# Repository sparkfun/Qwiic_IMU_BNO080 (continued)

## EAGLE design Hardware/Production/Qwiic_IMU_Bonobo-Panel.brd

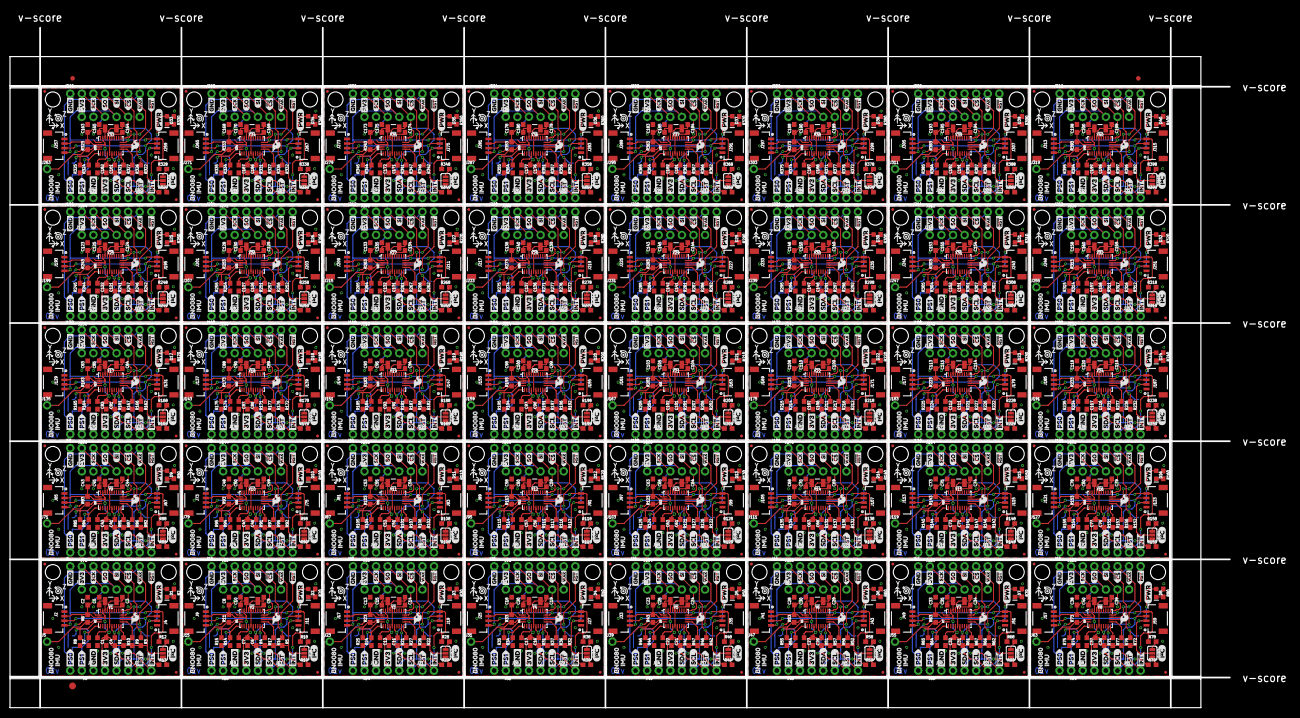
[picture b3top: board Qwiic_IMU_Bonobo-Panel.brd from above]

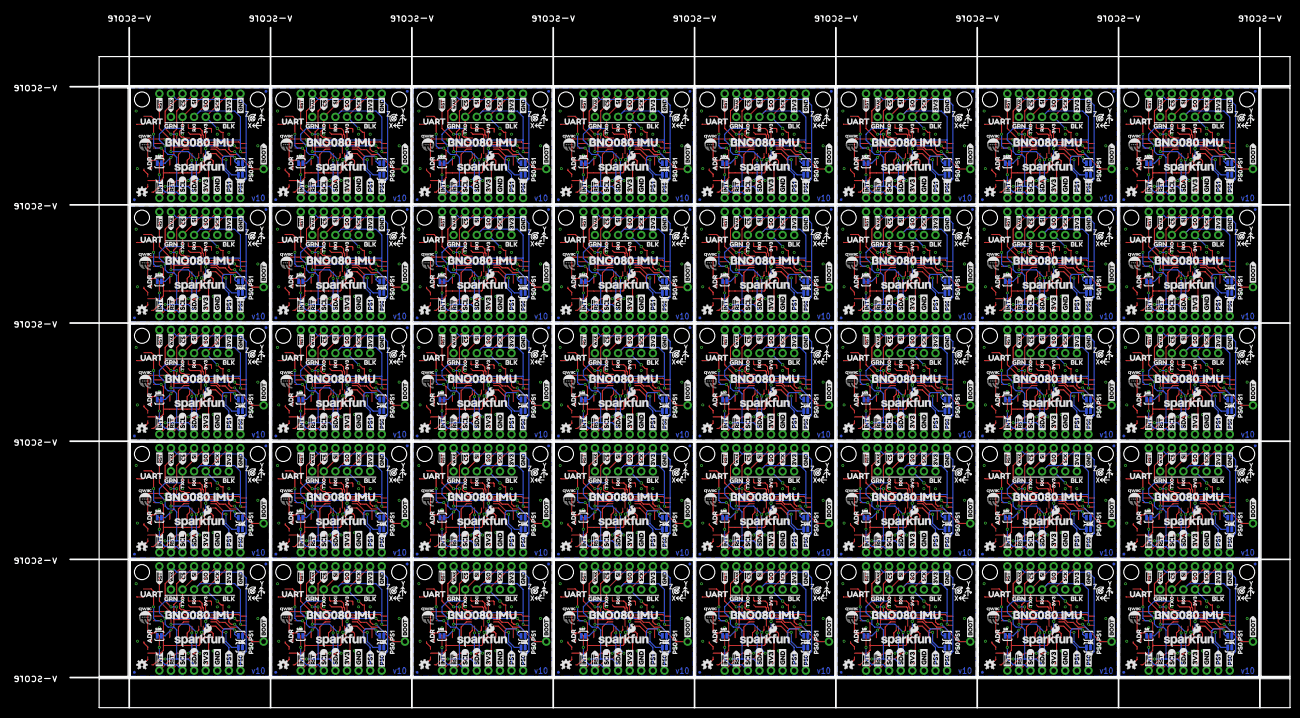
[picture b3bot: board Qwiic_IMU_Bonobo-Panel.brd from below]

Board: 2 copper layers, 267.5 x 149.1 mm, 3483 parts (1400 on the bottom side), 760 nets.

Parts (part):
C1, C2, C4, C6, C7, C8, C11, C12, C13, C16, C17, C18, C21, C22, C23, C26, C27, C28, C31, C32, C33, C36, C37, C38, C41, C42, C43, C46, C47, C48, C51, C52, C53, C56, C57, C58, C61, C62, C63, C66, C67, C68, C71, C72, C73, C76, C77, C78, C81, C82, C83, C86, C87, C88, C91, C92, C93, C96, C97, C98, C101, C102, C103, C106, C107, C108, C111, C112, C113, C116, C117, C118, C121, C122, C123, C126, C127, C128, C131, C132, C133, C136, C137, C138, C141, C142, C143, C146, C147, C148, C151, C152, C153, C156, C157, C158, C161, C162, C163, C166, C167, C168, C171, C172, C173, C176, C177, C178, C181, C182, C183, C186, C187, C188, C191, C192, C193, C196, C197, C198: 0.1uF; 0603
C3, C5, C9, C10, C14, C15, C19, C20, C24, C25, C29, C30, C34, C35, C39, C40, C44, C45, C49, C50, C54, C55, C59, C60, C64, C65, C69, C70, C74, C75, C79, C80, C84, C85, C89, C90, C94, C95, C99, C100, C104, C105, C109, C110, C114, C115, C119, C120, C124, C125, C129, C130, C134, C135, C139, C140, C144, C145, C149, C150, C154, C155, C159, C160, C164, C165, C169, C170, C174, C175, C179, C180, C184, C185, C189, C190, C194, C195, C199, C200: 22pF; 0603
D1, D2, D3, D4, D5, D6, D7, D8, D9, D10, D11, D12, D13, D14, D15, D16, D17, D18, D19, D20, D21, D22, D23, D24, D25, D26, D27, D28, D29, D30, D31, D32, D33, D34, D35, D36, D37, D38, D39, D40: RED; LED-0603
E$1, E$2: FIDUCIAL-1X2
E$3: FIDUCIAL-1.5X3
J1, J14, J22, J30, J38, J46, J54, J62, J70, J78, J86, J94, J102, J110, J118, J126, J134, J142, J150, J158, J166, J174, J182, J190, J198, J206, J214, J222, J230, J238, J246, J254, J262, J270, J278, J286, J294, J302, J310, J318: 1X06_NO_SILK
J2, J4, J9, J11, J17, J19, J25, J27, J33, J35, J41, J43, J49, J51, J57, J59, J65, J67, J73, J75, J81, J83, J89, J91, J97, J99, J105, J107, J113, J115, J121, J123, J129, J131, J137, J139, J145, J147, J153, J155, J161, J163, J169, J171, J177, J179, J185, J187, J193, J195, J201, J203, J209, J211, J217, J219, J225, J227, J233, J235, J241, J243, J249, J251, J257, J259, J265, J267, J273, J275, J281, J283, J289, J291, J297, J299, J305, J307, J313, J315: SMD; 1X04_1MM_RA
J3, J10, J18, J26, J34, J42, J50, J58, J66, J74, J82, J90, J98, J106, J114, J122, J130, J138, J146, J154, J162, J170, J178, J186, J194, J202, J210, J218, J226, J234, J242, J250, J258, J266, J274, J282, J290, J298, J306, J314: PTH; 1X04_NO_SILK
J5, J15, J23, J31, J39, J47, J55, J63, J71, J79, J87, J95, J103, J111, J119, J127, J135, J143, J151, J159, J167, J175, J183, J191, J199, J207, J215, J223, J231, J239, J247, J255, J263, J271, J279, J287, J295, J303, J311, J319: 1X01_NO_SILK
J6, J12, J20, J28, J36, J44, J52, J60, J68, J76, J84, J92, J100, J108, J116, J124, J132, J140, J148, J156, J164, J172, J180, J188, J196, J204, J212, J220, J228, J236, J244, J252, J260, J268, J276, J284, J292, J300, J308, J316: SPI; 1X08_NO_SILK
J7, J8, J13, J16, J21, J24, J29, J32, J37, J40, J45, J48, J53, J56, J61, J64, J69, J72, J77, J80, J85, J88, J93, J96, J101, J104, J109, J112, J117, J120, J125, J128, J133, J136, J141, J144, J149, J152, J157, J160, J165, J168, J173, J176, J181, J184, J189, J192, J197, J200, J205, J208, J213, J216, J221, J224, J229, J232, J237, J240, J245, J248, J253, J256, J261, J264, J269, J272, J277, J280, J285, J288, J293, J296, J301, J304, J309, J312, J317, J320: 1X02_NO_SILK
JP1, JP2, JP5, JP6, JP9, JP10, JP11, JP12, JP15, JP16, JP17, JP18, JP21, JP22, JP23, JP24, JP27, JP28, JP29, JP30, JP33, JP34, JP35, JP36, JP39, JP40, JP41, JP42, JP45, JP46, JP47, JP48, JP51, JP52, JP53, JP54, JP57, JP58, JP59, JP60, JP63, JP64, JP65, JP66, JP69, JP70, JP71, JP72, JP75, JP76, JP77, JP78, JP81, JP82, JP83, JP84, JP87, JP88, JP89, JP90, JP93, JP94, JP95, JP96, JP99, JP100, JP101, JP102, JP105, JP106, JP107, JP108, JP111, JP112, JP113, JP114, JP117, JP118, JP119, JP120, JP123, JP124, JP125, JP126, JP129, JP130, JP131, JP132, JP135, JP136, JP137, JP138, JP141, JP142, JP143, JP144, JP147, JP148, JP149, JP150, JP153, JP154, JP155, JP156, JP159, JP160, JP161, JP162, JP165, JP166, JP167, JP168, JP171, JP172, JP173, JP174, JP177, JP178, JP179, JP180, JP183, JP184, JP185, JP186, JP189, JP190, JP191, JP192, JP195, JP196, JP197, JP198, JP201, JP202, JP203, JP204, JP207, JP208, JP209, JP210, JP213, JP214, JP215, JP216, JP219, JP220, JP221, JP222, JP225, JP226, JP227, JP228, JP231, JP232, JP233, JP234, JP237, JP238, JP239, JP240: FIDUCIALUFIDUCIAL; MICRO-FIDUCIAL
JP3, JP4, JP7, JP8, JP13, JP14, JP19, JP20, JP25, JP26, JP31, JP32, JP37, JP38, JP43, JP44, JP49, JP50, JP55, JP56, JP61, JP62, JP67, JP68, JP73, JP74, JP79, JP80, JP85, JP86, JP91, JP92, JP97, JP98, JP103, JP104, JP109, JP110, JP115, JP116, JP121, JP122, JP127, JP128, JP133, JP134, JP139, JP140, JP145, JP146, JP151, JP152, JP157, JP158, JP163, JP164, JP169, JP170, JP175, JP176, JP181, JP182, JP187, JP188, JP193, JP194, JP199, JP200, JP205, JP206, JP211, JP212, JP217, JP218, JP223, JP224, JP229, JP230, JP235, JP236: STAND-OFF
LOGO1, LOGO2, LOGO7, LOGO10, LOGO13, LOGO16, LOGO19, LOGO22, LOGO25, LOGO28, LOGO31, LOGO34, LOGO37, LOGO40, LOGO43, LOGO46, LOGO49, LOGO52, LOGO55, LOGO58, LOGO61, LOGO64, LOGO67, LOGO70, LOGO73, LOGO76, LOGO79, LOGO82, LOGO85, LOGO88, LOGO91, LOGO94, LOGO97, LOGO100, LOGO103, LOGO106, LOGO109, LOGO112, LOGO115, LOGO118: OSHW-LOGOMINI; OSHW-LOGO-MINI
LOGO3, LOGO4, LOGO8, LOGO11, LOGO14, LOGO17, LOGO20, LOGO23, LOGO26, LOGO29, LOGO32, LOGO35, LOGO38, LOGO41, LOGO44, LOGO47, LOGO50, LOGO53, LOGO56, LOGO59, LOGO62, LOGO65, LOGO68, LOGO71, LOGO74, LOGO77, LOGO80, LOGO83, LOGO86, LOGO89, LOGO92, LOGO95, LOGO98, LOGO101, LOGO104, LOGO107, LOGO110, LOGO113, LOGO116, LOGO119: SFE_LOGO_FLAME.1_INCH; SFE_LOGO_FLAME_.1
LOGO5, LOGO6, LOGO9, LOGO12, LOGO15, LOGO18, LOGO21, LOGO24, LOGO27, LOGO30, LOGO33, LOGO36, LOGO39, LOGO42, LOGO45, LOGO48, LOGO51, LOGO54, LOGO57, LOGO60, LOGO63, LOGO66, LOGO69, LOGO72, LOGO75, LOGO78, LOGO81, LOGO84, LOGO87, LOGO90, LOGO93, LOGO96, LOGO99, LOGO102, LOGO105, LOGO108, LOGO111, LOGO114, LOGO117, LOGO120: SFE_LOGO_NAME_FLAME.1_INCH; SFE_LOGO_NAME_FLAME_.1
R1, R3, R4, R5, R6, R7, R8, R11, R14, R15, R21, R22, R23, R24, R25, R31, R32, R33, R34, R35, R41, R42, R43, R44, R45, R51, R52, R53, R54, R55, R61, R62, R63, R64, R65, R71, R72, R73, R74, R75, R81, R82, R83, R84, R85, R91, R92, R93, R94, R95, R101, R102, R103, R104, R105, R111, R112, R113, R114, R115, R121, R122, R123, R124, R125, R131, R132, R133, R134, R135, R141, R142, R143, R144, R145, R151, R152, R153, R154, R155, R161, R162, R163, R164, R165, R171, R172, R173, R174, R175, R181, R182, R183, R184, R185, R191, R192, R193, R194, R195, R201, R202, R203, R204, R205, R211, R212, R213, R214, R215, R221, R222, R223, R224, R225, R231, R232, R233, R234, R235, R241, R242, R243, R244, R245, R251, R252, R253, R254, R255, R261, R262, R263, R264, R265, R271, R272, R273, R274, R275, R281, R282, R283, R284, R285, R291, R292, R293, R294, R295, R301, R302, R303, R304, R305, R311, R312, R313, R314, R315, R321, R322, R323, R324, R325, R331, R332, R333, R334, R335, R341, R342, R343, R344, R345, R351, R352, R353, R354, R355, R361, R362, R363, R364, R365, R371, R372, R373, R374, R375, R381, R382, R383, R384, R385, R391, R392, R393, R394, R395: 10k; 0603
R2, R20, R30, R40, R50, R60, R70, R80, R90, R100, R110, R120, R130, R140, R150, R160, R170, R180, R190, R200, R210, R220, R230, R240, R250, R260, R270, R280, R290, R300, R310, R320, R330, R340, R350, R360, R370, R380, R390, R400: 1k; 0603
R9, R10, R16, R17, R26, R27, R36, R37, R46, R47, R56, R57, R66, R67, R76, R77, R86, R87, R96, R97, R106, R107, R116, R117, R126, R127, R136, R137, R146, R147, R156, R157, R166, R167, R176, R177, R186, R187, R196, R197, R206, R207, R216, R217, R226, R227, R236, R237, R246, R247, R256, R257, R266, R267, R276, R277, R286, R287, R296, R297, R306, R307, R316, R317, R326, R327, R336, R337, R346, R347, R356, R357, R366, R367, R376, R377, R386, R387, R396, R397: 4.7k; 0603
R12, R13, R18, R19, R28, R29, R38, R39, R48, R49, R58, R59, R68, R69, R78, R79, R88, R89, R98, R99, R108, R109, R118, R119, R128, R129, R138, R139, R148, R149, R158, R159, R168, R169, R178, R179, R188, R189, R198, R199, R208, R209, R218, R219, R228, R229, R238, R239, R248, R249, R258, R259, R268, R269, R278, R279, R288, R289, R298, R299, R308, R309, R318, R319, R328, R329, R338, R339, R348, R349, R358, R359, R368, R369, R378, R379, R388, R389, R398, R399: 2.2k; 0603
SJ1, SJ8, SJ12, SJ16, SJ20, SJ24, SJ28, SJ32, SJ36, SJ40, SJ44, SJ48, SJ52, SJ56, SJ60, SJ64, SJ68, SJ72, SJ76, SJ80, SJ84, SJ88, SJ92, SJ96, SJ100, SJ104, SJ108, SJ112, SJ116, SJ120, SJ124, SJ128, SJ132, SJ136, SJ140, SJ144, SJ148, SJ152, SJ156, SJ160: SMT-JUMPER_3_2-NC_PASTE_SILK
SJ2, SJ3, SJ4, SJ5, SJ6, SJ7, SJ9, SJ10, SJ11, SJ13, SJ14, SJ15, SJ17, SJ18, SJ19, SJ21, SJ22, SJ23, SJ25, SJ26, SJ27, SJ29, SJ30, SJ31, SJ33, SJ34, SJ35, SJ37, SJ38, SJ39, SJ41, SJ42, SJ43, SJ45, SJ46, SJ47, SJ49, SJ50, SJ51, SJ53, SJ54, SJ55, SJ57, SJ58, SJ59, SJ61, SJ62, SJ63, SJ65, SJ66, SJ67, SJ69, SJ70, SJ71, SJ73, SJ74, SJ75, SJ77, SJ78, SJ79, SJ81, SJ82, SJ83, SJ85, SJ86, SJ87, SJ89, SJ90, SJ91, SJ93, SJ94, SJ95, SJ97, SJ98, SJ99, SJ101, SJ102, SJ103, SJ105, SJ106, SJ107, SJ109, SJ110, SJ111, SJ113, SJ114, SJ115, SJ117, SJ118, SJ119, SJ121, SJ122, SJ123, SJ125, SJ126, SJ127, SJ129, SJ130, SJ131, SJ133, SJ134, SJ135, SJ137, SJ138, SJ139, SJ141, SJ142, SJ143, SJ145, SJ146, SJ147, SJ149, SJ150, SJ151, SJ153, SJ154, SJ155, SJ157, SJ158, SJ159: SJ_2S-NO
U1, U2, U3, U4, U5, U6, U7, U8, U9, U10, U11, U12, U13, U14, U15, U16, U17, U18, U19, U20, U21, U22, U23, U24, U25, U26, U27, U28, U29, U30, U31, U32, U33, U34, U35, U36, U37, U38, U39, U40: BNO080; LGA-28
U$1, U$95, U$143, U$191, U$239, U$287, U$335, U$383, U$431, U$479, U$527, U$575, U$623, U$671, U$719, U$767, U$815, U$863, U$911, U$959, U$1007, U$1055, U$1103, U$1151, U$1199, U$1247, U$1295, U$1343, U$1391, U$1439, U$1487, U$1535, U$1583, U$1631, U$1679, U$1727, U$1775, U$1823, U$1871, U$1919: (PWR)
U$2, U$94, U$142, U$190, U$238, U$286, U$334, U$382, U$430, U$478, U$526, U$574, U$622, U$670, U$718, U$766, U$814, U$862, U$910, U$958, U$1006, U$1054, U$1102, U$1150, U$1198, U$1246, U$1294, U$1342, U$1390, U$1438, U$1486, U$1534, U$1582, U$1630, U$1678, U$1726, U$1774, U$1822, U$1870, U$1918: BOOT2
U$3, U$4, U$24, U$31, U$97, U$98, U$145, U$146, U$193, U$194, U$241, U$242, U$289, U$290, U$337, U$338, U$385, U$386, U$433, U$434, U$481, U$482, U$529, U$530, U$577, U$578, U$625, U$626, U$673, U$674, U$721, U$722, U$769, U$770, U$817, U$818, U$865, U$866, U$913, U$914, U$961, U$962, U$1009, U$1010, U$1057, U$1058, U$1105, U$1106, U$1153, U$1154, U$1201, U$1202, U$1249, U$1250, U$1297, U$1298, U$1345, U$1346, U$1393, U$1394, U$1441, U$1442, U$1489, U$1490, U$1537, U$1538, U$1585, U$1586, U$1633, U$1634, U$1681, U$1682, U$1729, U$1730, U$1777, U$1778, U$1825, U$1826, U$1873, U$1874: #RST>
U$5, U$6, U$32, U$36, U$99, U$100, U$147, U$148, U$195, U$196, U$243, U$244, U$291, U$292, U$339, U$340, U$387, U$388, U$435, U$436, U$483, U$484, U$531, U$532, U$579, U$580, U$627, U$628, U$675, U$676, U$723, U$724, U$771, U$772, U$819, U$820, U$867, U$868, U$915, U$916, U$963, U$964, U$1011, U$1012, U$1059, U$1060, U$1107, U$1108, U$1155, U$1156, U$1203, U$1204, U$1251, U$1252, U$1299, U$1300, U$1347, U$1348, U$1395, U$1396, U$1443, U$1444, U$1491, U$1492, U$1539, U$1540, U$1587, U$1588, U$1635, U$1636, U$1683, U$1684, U$1731, U$1732, U$1779, U$1780, U$1827, U$1828, U$1875, U$1876: SCL
U$7, U$8, U$37, U$38, U$101, U$102, U$149, U$150, U$197, U$198, U$245, U$246, U$293, U$294, U$341, U$342, U$389, U$390, U$437, U$438, U$485, U$486, U$533, U$534, U$581, U$582, U$629, U$630, U$677, U$678, U$725, U$726, U$773, U$774, U$821, U$822, U$869, U$870, U$917, U$918, U$965, U$966, U$1013, U$1014, U$1061, U$1062, U$1109, U$1110, U$1157, U$1158, U$1205, U$1206, U$1253, U$1254, U$1301, U$1302, U$1349, U$1350, U$1397, U$1398, U$1445, U$1446, U$1493, U$1494, U$1541, U$1542, U$1589, U$1590, U$1637, U$1638, U$1685, U$1686, U$1733, U$1734, U$1781, U$1782, U$1829, U$1830, U$1877, U$1878: SDA
U$9, U$10, U$45, U$48, U$103, U$104, U$151, U$152, U$199, U$200, U$247, U$248, U$295, U$296, U$343, U$344, U$391, U$392, U$439, U$440, U$487, U$488, U$535, U$536, U$583, U$584, U$631, U$632, U$679, U$680, U$727, U$728, U$775, U$776, U$823, U$824, U$871, U$872, U$919, U$920, U$967, U$968, U$1015, U$1016, U$1063, U$1064, U$1111, U$1112, U$1159, U$1160, U$1207, U$1208, U$1255, U$1256, U$1303, U$1304, U$1351, U$1352, U$1399, U$1400, U$1447, U$1448, U$1495, U$1496, U$1543, U$1544, U$1591, U$1592, U$1639, U$1640, U$1687, U$1688, U$1735, U$1736, U$1783, U$1784, U$1831, U$1832, U$1879, U$1880: 3V3
U$11, U$50, U$73, U$74, U$121, U$122, U$169, U$170, U$217, U$218, U$265, U$266, U$313, U$314, U$361, U$362, U$409, U$410, U$457, U$458, U$505, U$506, U$553, U$554, U$601, U$602, U$649, U$650, U$697, U$698, U$745, U$746, U$793, U$794, U$841, U$842, U$889, U$890, U$937, U$938, U$985, U$986, U$1033, U$1034, U$1081, U$1082, U$1129, U$1130, U$1177, U$1178, U$1225, U$1226, U$1273, U$1274, U$1321, U$1322, U$1369, U$1370, U$1417, U$1418, U$1465, U$1466, U$1513, U$1514, U$1561, U$1562, U$1609, U$1610, U$1657, U$1658, U$1705, U$1706, U$1753, U$1754, U$1801, U$1802, U$1849, U$1850, U$1897, U$1898: 3V30
U$12, U$13, U$83, U$84, U$131, U$132, U$179, U$180, U$227, U$228, U$275, U$276, U$323, U$324, U$371, U$372, U$419, U$420, U$467, U$468, U$515, U$516, U$563, U$564, U$611, U$612, U$659, U$660, U$707, U$708, U$755, U$756, U$803, U$804, U$851, U$852, U$899, U$900, U$947, U$948, U$995, U$996, U$1043, U$1044, U$1091, U$1092, U$1139, U$1140, U$1187, U$1188, U$1235, U$1236, U$1283, U$1284, U$1331, U$1332, U$1379, U$1380, U$1427, U$1428, U$1475, U$1476, U$1523, U$1524, U$1571, U$1572, U$1619, U$1620, U$1667, U$1668, U$1715, U$1716, U$1763, U$1764, U$1811, U$1812, U$1859, U$1860, U$1907, U$1908: SCK0
U$14, U$89, U$137, U$185, U$233, U$281, U$329, U$377, U$425, U$473, U$521, U$569, U$617, U$665, U$713, U$761, U$809, U$857, U$905, U$953, U$1001, U$1049, U$1097, U$1145, U$1193, U$1241, U$1289, U$1337, U$1385, U$1433, U$1481, U$1529, U$1577, U$1625, U$1673, U$1721, U$1769, U$1817, U$1865, U$1913: PS03
U$15, U$16, U$56, U$57, U$105, U$106, U$153, U$154, U$201, U$202, U$249, U$250, U$297, U$298, U$345, U$346, U$393, U$394, U$441, U$442, U$489, U$490, U$537, U$538, U$585, U$586, U$633, U$634, U$681, U$682, U$729, U$730, U$777, U$778, U$825, U$826, U$873, U$874, U$921, U$922, U$969, U$970, U$1017, U$1018, U$1065, U$1066, U$1113, U$1114, U$1161, U$1162, U$1209, U$1210, U$1257, U$1258, U$1305, U$1306, U$1353, U$1354, U$1401, U$1402, U$1449, U$1450, U$1497, U$1498, U$1545, U$1546, U$1593, U$1594, U$1641, U$1642, U$1689, U$1690, U$1737, U$1738, U$1785, U$1786, U$1833, U$1834, U$1881, U$1882: GND
U$17, U$18, U$85, U$86, U$133, U$134, U$181, U$182, U$229, U$230, U$277, U$278, U$325, U$326, U$373, U$374, U$421, U$422, U$469, U$470, U$517, U$518, U$565, U$566, U$613, U$614, U$661, U$662, U$709, U$710, U$757, U$758, U$805, U$806, U$853, U$854, U$901, U$902, U$949, U$950, U$997, U$998, U$1045, U$1046, U$1093, U$1094, U$1141, U$1142, U$1189, U$1190, U$1237, U$1238, U$1285, U$1286, U$1333, U$1334, U$1381, U$1382, U$1429, U$1430, U$1477, U$1478, U$1525, U$1526, U$1573, U$1574, U$1621, U$1622, U$1669, U$1670, U$1717, U$1718, U$1765, U$1766, U$1813, U$1814, U$1861, U$1862, U$1909, U$1910: SI1
U$19, U$20, U$77, U$78, U$125, U$126, U$173, U$174, U$221, U$222, U$269, U$270, U$317, U$318, U$365, U$366, U$413, U$414, U$461, U$462, U$509, U$510, U$557, U$558, U$605, U$606, U$653, U$654, U$701, U$702, U$749, U$750, U$797, U$798, U$845, U$846, U$893, U$894, U$941, U$942, U$989, U$990, U$1037, U$1038, U$1085, U$1086, U$1133, U$1134, U$1181, U$1182, U$1229, U$1230, U$1277, U$1278, U$1325, U$1326, U$1373, U$1374, U$1421, U$1422, U$1469, U$1470, U$1517, U$1518, U$1565, U$1566, U$1613, U$1614, U$1661, U$1662, U$1709, U$1710, U$1757, U$1758, U$1805, U$1806, U$1853, U$1854, U$1901, U$1902: #WAK6
U$21, U$90, U$138, U$186, U$234, U$282, U$330, U$378, U$426, U$474, U$522, U$570, U$618, U$666, U$714, U$762, U$810, U$858, U$906, U$954, U$1002, U$1050, U$1098, U$1146, U$1194, U$1242, U$1290, U$1338, U$1386, U$1434, U$1482, U$1530, U$1578, U$1626, U$1674, U$1722, U$1770, U$1818, U$1866, U$1914: 3V32
U$22, U$91, U$139, U$187, U$235, U$283, U$331, U$379, U$427, U$475, U$523, U$571, U$619, U$667, U$715, U$763, U$811, U$859, U$907, U$955, U$1003, U$1051, U$1099, U$1147, U$1195, U$1243, U$1291, U$1339, U$1387, U$1435, U$1483, U$1531, U$1579, U$1627, U$1675, U$1723, U$1771, U$1819, U$1867, U$1915: RXI1
U$23, U$58, U$107, U$155, U$203, U$251, U$299, U$347, U$395, U$443, U$491, U$539, U$587, U$635, U$683, U$731, U$779, U$827, U$875, U$923, U$971, U$1019, U$1067, U$1115, U$1163, U$1211, U$1259, U$1307, U$1355, U$1403, U$1451, U$1499, U$1547, U$1595, U$1643, U$1691, U$1739, U$1787, U$1835, U$1883: (I_SUPER2_C)
U$25, U$26, U$60, U$61, U$108, U$109, U$156, U$157, U$204, U$205, U$252, U$253, U$300, U$301, U$348, U$349, U$396, U$397, U$444, U$445, U$492, U$493, U$540, U$541, U$588, U$589, U$636, U$637, U$684, U$685, U$732, U$733, U$780, U$781, U$828, U$829, U$876, U$877, U$924, U$925, U$972, U$973, U$1020, U$1021, U$1068, U$1069, U$1116, U$1117, U$1164, U$1165, U$1212, U$1213, U$1260, U$1261, U$1308, U$1309, U$1356, U$1357, U$1404, U$1405, U$1452, U$1453, U$1500, U$1501, U$1548, U$1549, U$1596, U$1597, U$1644, U$1645, U$1692, U$1693, U$1740, U$1741, U$1788, U$1789, U$1836, U$1837, U$1884, U$1885: #INT0
U$27, U$28, U$62, U$63, U$110, U$111, U$158, U$159, U$206, U$207, U$254, U$255, U$302, U$303, U$350, U$351, U$398, U$399, U$446, U$447, U$494, U$495, U$542, U$543, U$590, U$591, U$638, U$639, U$686, U$687, U$734, U$735, U$782, U$783, U$830, U$831, U$878, U$879, U$926, U$927, U$974, U$975, U$1022, U$1023, U$1070, U$1071, U$1118, U$1119, U$1166, U$1167, U$1214, U$1215, U$1262, U$1263, U$1310, U$1311, U$1358, U$1359, U$1406, U$1407, U$1454, U$1455, U$1502, U$1503, U$1550, U$1551, U$1598, U$1599, U$1646, U$1647, U$1694, U$1695, U$1742, U$1743, U$1790, U$1791, U$1838, U$1839, U$1886, U$1887: PS14
U$29, U$64, U$112, U$160, U$208, U$256, U$304, U$352, U$400, U$448, U$496, U$544, U$592, U$640, U$688, U$736, U$784, U$832, U$880, U$928, U$976, U$1024, U$1072, U$1120, U$1168, U$1216, U$1264, U$1312, U$1360, U$1408, U$1456, U$1504, U$1552, U$1600, U$1648, U$1696, U$1744, U$1792, U$1840, U$1888: PS05
U$30, U$93, U$141, U$189, U$237, U$285, U$333, U$381, U$429, U$477, U$525, U$573, U$621, U$669, U$717, U$765, U$813, U$861, U$909, U$957, U$1005, U$1053, U$1101, U$1149, U$1197, U$1245, U$1293, U$1341, U$1389, U$1437, U$1485, U$1533, U$1581, U$1629, U$1677, U$1725, U$1773, U$1821, U$1869, U$1917: ADR0
U$33, U$65, U$113, U$161, U$209, U$257, U$305, U$353, U$401, U$449, U$497, U$545, U$593, U$641, U$689, U$737, U$785, U$833, U$881, U$929, U$977, U$1025, U$1073, U$1121, U$1169, U$1217, U$1265, U$1313, U$1361, U$1409, U$1457, U$1505, U$1553, U$1601, U$1649, U$1697, U$1745, U$1793, U$1841, U$1889: PS114
U$34, U$66, U$114, U$162, U$210, U$258, U$306, U$354, U$402, U$450, U$498, U$546, U$594, U$642, U$690, U$738, U$786, U$834, U$882, U$930, U$978, U$1026, U$1074, U$1122, U$1170, U$1218, U$1266, U$1314, U$1362, U$1410, U$1458, U$1506, U$1554, U$1602, U$1650, U$1698, U$1746, U$1794, U$1842, U$1890: PS015
U$35, U$92, U$140, U$188, U$236, U$284, U$332, U$380, U$428, U$476, U$524, U$572, U$620, U$668, U$716, U$764, U$812, U$860, U$908, U$956, U$1004, U$1052, U$1100, U$1148, U$1196, U$1244, U$1292, U$1340, U$1388, U$1436, U$1484, U$1532, U$1580, U$1628, U$1676, U$1724, U$1772, U$1820, U$1868, U$1916: TXO0
U$39, U$67, U$115, U$163, U$211, U$259, U$307, U$355, U$403, U$451, U$499, U$547, U$595, U$643, U$691, U$739, U$787, U$835, U$883, U$931, U$979, U$1027, U$1075, U$1123, U$1171, U$1219, U$1267, U$1315, U$1363, U$1411, U$1459, U$1507, U$1555, U$1603, U$1651, U$1699, U$1747, U$1795, U$1843, U$1891: UART8
U$40, U$68, U$116, U$164, U$212, U$260, U$308, U$356, U$404, U$452, U$500, U$548, U$596, U$644, U$692, U$740, U$788, U$836, U$884, U$932, U$980, U$1028, U$1076, U$1124, U$1172, U$1220, U$1268, U$1316, U$1364, U$1412, U$1460, U$1508, U$1556, U$1604, U$1652, U$1700, U$1748, U$1796, U$1844, U$1892: GRN10
U$41, U$69, U$117, U$165, U$213, U$261, U$309, U$357, U$405, U$453, U$501, U$549, U$597, U$645, U$693, U$741, U$789, U$837, U$885, U$933, U$981, U$1029, U$1077, U$1125, U$1173, U$1221, U$1269, U$1317, U$1365, U$1413, U$1461, U$1509, U$1557, U$1605, U$1653, U$1701, U$1749, U$1797, U$1845, U$1893: BLK9
U$42, U$43, U$79, U$80, U$127, U$128, U$175, U$176, U$223, U$224, U$271, U$272, U$319, U$320, U$367, U$368, U$415, U$416, U$463, U$464, U$511, U$512, U$559, U$560, U$607, U$608, U$655, U$656, U$703, U$704, U$751, U$752, U$799, U$800, U$847, U$848, U$895, U$896, U$943, U$944, U$991, U$992, U$1039, U$1040, U$1087, U$1088, U$1135, U$1136, U$1183, U$1184, U$1231, U$1232, U$1279, U$1280, U$1327, U$1328, U$1375, U$1376, U$1423, U$1424, U$1471, U$1472, U$1519, U$1520, U$1567, U$1568, U$1615, U$1616, U$1663, U$1664, U$1711, U$1712, U$1759, U$1760, U$1807, U$1808, U$1855, U$1856, U$1903, U$1904: GND1
U$44, U$70, U$118, U$166, U$214, U$262, U$310, U$358, U$406, U$454, U$502, U$550, U$598, U$646, U$694, U$742, U$790, U$838, U$886, U$934, U$982, U$1030, U$1078, U$1126, U$1174, U$1222, U$1270, U$1318, U$1366, U$1414, U$1462, U$1510, U$1558, U$1606, U$1654, U$1702, U$1750, U$1798, U$1846, U$1894: BNO080_IMU11
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
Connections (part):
3.3V: C2.1, C4.1, D1.A, J1.3, J2.2, J3.2, J4.2, J6.2, R1.2, R3.2, R6.2, R9.2, R10.2, SJ1.2, SJ3.1, SJ4.1, U2.3, U2.28
3.3V1: C6.1, C8.1, D2.A, J9.2, J10.2, J11.2, J12.2, J14.3, R4.2, R5.2, R11.2, R16.2, R17.2, SJ6.1, SJ7.1, SJ8.2, U1.3, U1.28
3.3V2: C11.1, C13.1, D3.A, J17.2, J18.2, J19.2, J20.2, J22.3, R21.2, R22.2, R23.2, R26.2, R27.2, SJ10.1, SJ11.1, SJ12.2, U3.3, U3.28
3.3V3: C16.1, C18.1, D4.A, J25.2, J26.2, J27.2, J28.2, J30.3, R31.2, R32.2, R33.2, R36.2, R37.2, SJ14.1, SJ15.1, SJ16.2, U4.3, U4.28
3.3V4: C21.1, C23.1, D5.A, J33.2, J34.2, J35.2, J36.2, J38.3, R41.2, R42.2, R43.2, R46.2, R47.2, SJ18.1, SJ19.1, SJ20.2, U5.3, U5.28
3.3V5: C26.1, C28.1, D6.A, J41.2, J42.2, J43.2, J44.2, J46.3, R51.2, R52.2, R53.2, R56.2, R57.2, SJ22.1, SJ23.1, SJ24.2, U6.3, U6.28
3.3V6: C31.1, C33.1, D7.A, J49.2, J50.2, J51.2, J52.2, J54.3, R61.2, R62.2, R63.2, R66.2, R67.2, SJ26.1, SJ27.1, SJ28.2, U7.3, U7.28
3.3V7: C36.1, C38.1, D8.A, J57.2, J58.2, J59.2, J60.2, J62.3, R71.2, R72.2, R73.2, R76.2, R77.2, SJ30.1, SJ31.1, SJ32.2, U8.3, U8.28
3.3V8: C41.1, C43.1, D9.A, J65.2, J66.2, J67.2, J68.2, J70.3, R81.2, R82.2, R83.2, R86.2, R87.2, SJ34.1, SJ35.1, SJ36.2, U9.3, U9.28
3.3V9: C46.1, C48.1, D10.A, J73.2, J74.2, J75.2, J76.2, J78.3, R91.2, R92.2, R93.2, R96.2, R97.2, SJ38.1, SJ39.1, SJ40.2, U10.3, U10.28
3.3V10: C51.1, C53.1, D11.A, J81.2, J82.2, J83.2, J84.2, J86.3, R101.2, R102.2, R103.2, R106.2, R107.2, SJ42.1, SJ43.1, SJ44.2, U11.3, U11.28
3.3V11: C56.1, C58.1, D12.A, J89.2, J90.2, J91.2, J92.2, J94.3, R111.2, R112.2, R113.2, R116.2, R117.2, SJ46.1, SJ47.1, SJ48.2, U12.3, U12.28
3.3V12: C61.1, C63.1, D13.A, J97.2, J98.2, J99.2, J100.2, J102.3, R121.2, R122.2, R123.2, R126.2, R127.2, SJ50.1, SJ51.1, SJ52.2, U13.3, U13.28
3.3V13: C66.1, C68.1, D14.A, J105.2, J106.2, J107.2, J108.2, J110.3, R131.2, R132.2, R133.2, R136.2, R137.2, SJ54.1, SJ55.1, SJ56.2, U14.3, U14.28
3.3V14: C71.1, C73.1, D15.A, J113.2, J114.2, J115.2, J116.2, J118.3, R141.2, R142.2, R143.2, R146.2, R147.2, SJ58.1, SJ59.1, SJ60.2, U15.3, U15.28
3.3V15: C76.1, C78.1, D16.A, J121.2, J122.2, J123.2, J124.2, J126.3, R151.2, R152.2, R153.2, R156.2, R157.2, SJ62.1, SJ63.1, SJ64.2, U16.3, U16.28
3.3V16: C81.1, C83.1, D17.A, J129.2, J130.2, J131.2, J132.2, J134.3, R161.2, R162.2, R163.2, R166.2, R167.2, SJ66.1, SJ67.1, SJ68.2, U17.3, U17.28
3.3V17: C86.1, C88.1, D18.A, J137.2, J138.2, J139.2, J140.2, J142.3, R171.2, R172.2, R173.2, R176.2, R177.2, SJ70.1, SJ71.1, SJ72.2, U18.3, U18.28
3.3V18: C91.1, C93.1, D19.A, J145.2, J146.2, J147.2, J148.2, J150.3, R181.2, R182.2, R183.2, R186.2, R187.2, SJ74.1, SJ75.1, SJ76.2, U19.3, U19.28
3.3V19: C96.1, C98.1, D20.A, J153.2, J154.2, J155.2, J156.2, J158.3, R191.2, R192.2, R193.2, R196.2, R197.2, SJ78.1, SJ79.1, SJ80.2, U20.3, U20.28
3.3V20: C101.1, C103.1, D21.A, J161.2, J162.2, J163.2, J164.2, J166.3, R201.2, R202.2, R203.2, R206.2, R207.2, SJ82.1, SJ83.1, SJ84.2, U21.3, U21.28
3.3V21: C106.1, C108.1, D22.A, J169.2, J170.2, J171.2, J172.2, J174.3, R211.2, R212.2, R213.2, R216.2, R217.2, SJ86.1, SJ87.1, SJ88.2, U22.3, U22.28
3.3V22: C111.1, C113.1, D23.A, J177.2, J178.2, J179.2, J180.2, J182.3, R221.2, R222.2, R223.2, R226.2, R227.2, SJ90.1, SJ91.1, SJ92.2, U23.3, U23.28
3.3V23: C116.1, C118.1, D24.A, J185.2, J186.2, J187.2, J188.2, J190.3, R231.2, R232.2, R233.2, R236.2, R237.2, SJ94.1, SJ95.1, SJ96.2, U24.3, U24.28
3.3V24: C121.1, C123.1, D25.A, J193.2, J194.2, J195.2, J196.2, J198.3, R241.2, R242.2, R243.2, R246.2, R247.2, SJ98.1, SJ99.1, SJ100.2, U25.3, U25.28
3.3V25: C126.1, C128.1, D26.A, J201.2, J202.2, J203.2, J204.2, J206.3, R251.2, R252.2, R253.2, R256.2, R257.2, SJ102.1, SJ103.1, SJ104.2, U26.3, U26.28
3.3V26: C131.1, C133.1, D27.A, J209.2, J210.2, J211.2, J212.2, J214.3, R261.2, R262.2, R263.2, R266.2, R267.2, SJ106.1, SJ107.1, SJ108.2, U27.3, U27.28
3.3V27: C136.1, C138.1, D28.A, J217.2, J218.2, J219.2, J220.2, J222.3, R271.2, R272.2, R273.2, R276.2, R277.2, SJ110.1, SJ111.1, SJ112.2, U28.3, U28.28
3.3V28: C141.1, C143.1, D29.A, J225.2, J226.2, J227.2, J228.2, J230.3, R281.2, R282.2, R283.2, R286.2, R287.2, SJ114.1, SJ115.1, SJ116.2, U29.3, U29.28
3.3V29: C146.1, C148.1, D30.A, J233.2, J234.2, J235.2, J236.2, J238.3, R291.2, R292.2, R293.2, R296.2, R297.2, SJ118.1, SJ119.1, SJ120.2, U30.3, U30.28
3.3V30: C151.1, C153.1, D31.A, J241.2, J242.2, J243.2, J244.2, J246.3, R301.2, R302.2, R303.2, R306.2, R307.2, SJ122.1, SJ123.1, SJ124.2, U31.3, U31.28
3.3V31: C156.1, C158.1, D32.A, J249.2, J250.2, J251.2, J252.2, J254.3, R311.2, R312.2, R313.2, R316.2, R317.2, SJ126.1, SJ127.1, SJ128.2, U32.3, U32.28
3.3V32: C161.1, C163.1, D33.A, J257.2, J258.2, J259.2, J260.2, J262.3, R321.2, R322.2, R323.2, R326.2, R327.2, SJ130.1, SJ131.1, SJ132.2, U33.3, U33.28
3.3V33: C166.1, C168.1, D34.A, J265.2, J266.2, J267.2, J268.2, J270.3, R331.2, R332.2, R333.2, R336.2, R337.2, SJ134.1, SJ135.1, SJ136.2, U34.3, U34.28
3.3V34: C171.1, C173.1, D35.A, J273.2, J274.2, J275.2, J276.2, J278.3, R341.2, R342.2, R343.2, R346.2, R347.2, SJ138.1, SJ139.1, SJ140.2, U35.3, U35.28
3.3V35: C176.1, C178.1, D36.A, J281.2, J282.2, J283.2, J284.2, J286.3, R351.2, R352.2, R353.2, R356.2, R357.2, SJ142.1, SJ143.1, SJ144.2, U36.3, U36.28
3.3V36: C181.1, C183.1, D37.A, J289.2, J290.2, J291.2, J292.2, J294.3, R361.2, R362.2, R363.2, R366.2, R367.2, SJ146.1, SJ147.1, SJ148.2, U37.3, U37.28
3.3V37: C186.1, C188.1, D38.A, J297.2, J298.2, J299.2, J300.2, J302.3, R371.2, R372.2, R373.2, R376.2, R377.2, SJ150.1, SJ151.1, SJ152.2, U38.3, U38.28
3.3V38: C191.1, C193.1, D39.A, J305.2, J306.2, J307.2, J308.2, J310.3, R381.2, R382.2, R383.2, R386.2, R387.2, SJ154.1, SJ155.1, SJ156.2, U39.3, U39.28
3.3V39: C196.1, C198.1, D40.A, J313.2, J314.2, J315.2, J316.2, J318.3, R391.2, R392.2, R393.2, R396.2, R397.2, SJ158.1, SJ159.1, SJ160.2, U40.3, U40.28
!BOOT: J5.1, R6.1, U2.4
!BOOT1: J15.1, R11.1, U1.4
!BOOT2: J23.1, R23.1, U3.4
!BOOT3: J31.1, R33.1, U4.4
!BOOT4: J39.1, R43.1, U5.4
!BOOT5: J47.1, R53.1, U6.4
!BOOT6: J55.1, R63.1, U7.4
!BOOT7: J63.1, R73.1, U8.4
!BOOT8: J71.1, R83.1, U9.4
!BOOT9: J79.1, R93.1, U10.4
!BOOT10: J87.1, R103.1, U11.4
!BOOT11: J95.1, R113.1, U12.4
!BOOT12: J103.1, R123.1, U13.4
!BOOT13: J111.1, R133.1, U14.4
!BOOT14: J119.1, R143.1, U15.4
!BOOT15: J127.1, R153.1, U16.4
!BOOT16: J135.1, R163.1, U17.4
!BOOT17: J143.1, R173.1, U18.4
!BOOT18: J151.1, R183.1, U19.4
!BOOT19: J159.1, R193.1, U20.4
!BOOT20: J167.1, R203.1, U21.4
!BOOT21: J175.1, R213.1, U22.4
!BOOT22: J183.1, R223.1, U23.4
!BOOT23: J191.1, R233.1, U24.4
!BOOT24: J199.1, R243.1, U25.4
!BOOT25: J207.1, R253.1, U26.4
!BOOT26: J215.1, R263.1, U27.4
!BOOT27: J223.1, R273.1, U28.4
!BOOT28: J231.1, R283.1, U29.4
!BOOT29: J239.1, R293.1, U30.4
!BOOT30: J247.1, R303.1, U31.4
!BOOT31: J255.1, R313.1, U32.4
!BOOT32: J263.1, R323.1, U33.4
!BOOT33: J271.1, R333.1, U34.4
!BOOT34: J279.1, R343.1, U35.4
!BOOT35: J287.1, R353.1, U36.4
!BOOT36: J295.1, R363.1, U37.4
!BOOT37: J303.1, R373.1, U38.4
!BOOT38: J311.1, R383.1, U39.4
!BOOT39: J319.1, R393.1, U40.4
!CS: J6.6, U2.18
!CS1: J12.6, U1.18
!CS2: J20.6, U3.18
!CS3: J28.6, U4.18
!CS4: J36.6, U5.18
!CS5: J44.6, U6.18
!CS6: J52.6, U7.18
!CS7: J60.6, U8.18
!CS8: J68.6, U9.18
!CS9: J76.6, U10.18
!CS10: J84.6, U11.18
!CS11: J92.6, U12.18
!CS12: J100.6, U13.18
!CS13: J108.6, U14.18
!CS14: J116.6, U15.18
!CS15: J124.6, U16.18
!CS16: J132.6, U17.18
!CS17: J140.6, U18.18
!CS18: J148.6, U19.18
!CS19: J156.6, U20.18
!CS20: J164.6, U21.18
!CS21: J172.6, U22.18
!CS22: J180.6, U23.18
!CS23: J188.6, U24.18
!CS24: J196.6, U25.18
!CS25: J204.6, U26.18
!CS26: J212.6, U27.18
!CS27: J220.6, U28.18
!CS28: J228.6, U29.18
!CS29: J236.6, U30.18
!CS30: J244.6, U31.18
!CS31: J252.6, U32.18
!CS32: J260.6, U33.18
!CS33: J268.6, U34.18
!CS34: J276.6, U35.18
!CS35: J284.6, U36.18
!CS36: J292.6, U37.18
!CS37: J300.6, U38.18
!CS38: J308.6, U39.18
!CS39: J316.6, U40.18
!INT: J7.2, U2.14
!INT1: J13.2, U1.14
!INT2: J21.2, U3.14
!INT3: J29.2, U4.14
!INT4: J37.2, U5.14
!INT5: J45.2, U6.14
!INT6: J53.2, U7.14
!INT7: J61.2, U8.14
!INT8: J69.2, U9.14
!INT9: J77.2, U10.14
!INT10: J85.2, U11.14
!INT11: J93.2, U12.14
!INT12: J101.2, U13.14
!INT13: J109.2, U14.14
!INT14: J117.2, U15.14
!INT15: J125.2, U16.14
!INT16: J133.2, U17.14
!INT17: J141.2, U18.14
!INT18: J149.2, U19.14
!INT19: J157.2, U20.14
!INT20: J165.2, U21.14
!INT21: J173.2, U22.14
!INT22: J181.2, U23.14
!INT23: J189.2, U24.14
!INT24: J197.2, U25.14
!INT25: J205.2, U26.14
!INT26: J213.2, U27.14
!INT27: J221.2, U28.14
!INT28: J229.2, U29.14
!INT29: J237.2, U30.14
!INT30: J245.2, U31.14
!INT31: J253.2, U32.14
!INT32: J261.2, U33.14
!INT33: J269.2, U34.14
!INT34: J277.2, U35.14
!INT35: J285.2, U36.14
!INT36: J293.2, U37.14
!INT37: J301.2, U38.14
!INT38: J309.2, U39.14
!INT39: J317.2, U40.14
!RST: J6.8, J7.1, R1.1, U2.11
!RST1: J12.8, J13.1, R4.1, U1.11
!RST2: J20.8, J21.1, R21.1, U3.11
!RST3: J28.8, J29.1, R31.1, U4.11
!RST4: J36.8, J37.1, R41.1, U5.11
!RST5: J44.8, J45.1, R51.1, U6.11
!RST6: J52.8, J53.1, R61.1, U7.11
!RST7: J60.8, J61.1, R71.1, U8.11
!RST8: J68.8, J69.1, R81.1, U9.11
!RST9: J76.8, J77.1, R91.1, U10.11
!RST10: J84.8, J85.1, R101.1, U11.11
!RST11: J92.8, J93.1, R111.1, U12.11
!RST12: J100.8, J101.1, R121.1, U13.11
!RST13: J108.8, J109.1, R131.1, U14.11
!RST14: J116.8, J117.1, R141.1, U15.11
!RST15: J124.8, J125.1, R151.1, U16.11
!RST16: J132.8, J133.1, R161.1, U17.11
!RST17: J140.8, J141.1, R171.1, U18.11
!RST18: J148.8, J149.1, R181.1, U19.11
!RST19: J156.8, J157.1, R191.1, U20.11
!RST20: J164.8, J165.1, R201.1, U21.11
!RST21: J172.8, J173.1, R211.1, U22.11
!RST22: J180.8, J181.1, R221.1, U23.11
!RST23: J188.8, J189.1, R231.1, U24.11
!RST24: J196.8, J197.1, R241.1, U25.11
!RST25: J204.8, J205.1, R251.1, U26.11
!RST26: J212.8, J213.1, R261.1, U27.11
!RST27: J220.8, J221.1, R271.1, U28.11
!RST28: J228.8, J229.1, R281.1, U29.11
!RST29: J236.8, J237.1, R291.1, U30.11
!RST30: J244.8, J245.1, R301.1, U31.11
!RST31: J252.8, J253.1, R311.1, U32.11
!RST32: J260.8, J261.1, R321.1, U33.11
!RST33: J268.8, J269.1, R331.1, U34.11
!RST34: J276.8, J277.1, R341.1, U35.11
!RST35: J284.8, J285.1, R351.1, U36.11
!RST36: J292.8, J293.1, R361.1, U37.11
!RST37: J300.8, J301.1, R371.1, U38.11
!RST38: J308.8, J309.1, R381.1, U39.11
!RST39: J316.8, J317.1, R391.1, U40.11
ADDR/MOSI: J6.5, R3.1, SJ2.2, U2.17
ADDR/MOSI1: J12.5, R5.1, SJ5.2, U1.17
ADDR/MOSI2: J20.5, R22.1, SJ9.2, U3.17
ADDR/MOSI3: J28.5, R32.1, SJ13.2, U4.17
ADDR/MOSI4: J36.5, R42.1, SJ17.2, U5.17
ADDR/MOSI5: J44.5, R52.1, SJ21.2, U6.17
ADDR/MOSI6: J52.5, R62.1, SJ25.2, U7.17
ADDR/MOSI7: J60.5, R72.1, SJ29.2, U8.17
ADDR/MOSI8: J68.5, R82.1, SJ33.2, U9.17
ADDR/MOSI9: J76.5, R92.1, SJ37.2, U10.17
ADDR/MOSI10: J84.5, R102.1, SJ41.2, U11.17
ADDR/MOSI11: J92.5, R112.1, SJ45.2, U12.17
ADDR/MOSI12: J100.5, R122.1, SJ49.2, U13.17
ADDR/MOSI13: J108.5, R132.1, SJ53.2, U14.17
ADDR/MOSI14: J116.5, R142.1, SJ57.2, U15.17
ADDR/MOSI15: J124.5, R152.1, SJ61.2, U16.17
ADDR/MOSI16: J132.5, R162.1, SJ65.2, U17.17
ADDR/MOSI17: J140.5, R172.1, SJ69.2, U18.17
ADDR/MOSI18: J148.5, R182.1, SJ73.2, U19.17
ADDR/MOSI19: J156.5, R192.1, SJ77.2, U20.17
ADDR/MOSI20: J164.5, R202.1, SJ81.2, U21.17
ADDR/MOSI21: J172.5, R212.1, SJ85.2, U22.17
ADDR/MOSI22: J180.5, R222.1, SJ89.2, U23.17
ADDR/MOSI23: J188.5, R232.1, SJ93.2, U24.17
ADDR/MOSI24: J196.5, R242.1, SJ97.2, U25.17
ADDR/MOSI25: J204.5, R252.1, SJ101.2, U26.17
ADDR/MOSI26: J212.5, R262.1, SJ105.2, U27.17
ADDR/MOSI27: J220.5, R272.1, SJ109.2, U28.17
ADDR/MOSI28: J228.5, R282.1, SJ113.2, U29.17
ADDR/MOSI29: J236.5, R292.1, SJ117.2, U30.17
ADDR/MOSI30: J244.5, R302.1, SJ121.2, U31.17
ADDR/MOSI31: J252.5, R312.1, SJ125.2, U32.17
ADDR/MOSI32: J260.5, R322.1, SJ129.2, U33.17
ADDR/MOSI33: J268.5, R332.1, SJ133.2, U34.17
ADDR/MOSI34: J276.5, R342.1, SJ137.2, U35.17
ADDR/MOSI35: J284.5, R352.1, SJ141.2, U36.17
ADDR/MOSI36: J292.5, R362.1, SJ145.2, U37.17
ADDR/MOSI37: J300.5, R372.1, SJ149.2, U38.17
ADDR/MOSI38: J308.5, R382.1, SJ153.2, U39.17
ADDR/MOSI39: J316.5, R392.1, SJ157.2, U40.17
CAP: C1.1, U2.9
CAP1: C7.1, U1.9
CAP2: C12.1, U3.9
CAP3: C17.1, U4.9
CAP4: C22.1, U5.9
CAP5: C27.1, U6.9
CAP6: C32.1, U7.9
CAP7: C37.1, U8.9
CAP8: C42.1, U9.9
CAP9: C47.1, U10.9
CAP10: C52.1, U11.9
CAP11: C57.1, U12.9
CAP12: C62.1, U13.9
CAP13: C67.1, U14.9
CAP14: C72.1, U15.9
CAP15: C77.1, U16.9
CAP16: C82.1, U17.9
CAP17: C87.1, U18.9
CAP18: C92.1, U19.9
CAP19: C97.1, U20.9
CAP20: C102.1, U21.9
CAP21: C107.1, U22.9
CAP22: C112.1, U23.9
CAP23: C117.1, U24.9
CAP24: C122.1, U25.9
CAP25: C127.1, U26.9
CAP26: C132.1, U27.9
CAP27: C137.1, U28.9
CAP28: C142.1, U29.9
CAP29: C147.1, U30.9
CAP30: C152.1, U31.9
CAP31: C157.1, U32.9
CAP32: C162.1, U33.9
CAP33: C167.1, U34.9
CAP34: C172.1, U35.9
CAP35: C177.1, U36.9
CAP36: C182.1, U37.9
CAP37: C187.1, U38.9
CAP38: C192.1, U39.9
CAP39: C197.1, U40.9
GND: C1.2, C2.2, C3.2, C4.2, C5.2, J1.1, J2.1, J3.1, J4.1, J6.1, R2.1, R7.1, R8.1, SJ2.1, U2.2, U2.10, U2.25
GND1: C6.2, C7.2, C8.2, C9.2, C10.2, J9.1, J10.1, J11.1, J12.1, J14.1, R14.1, R15.1, R20.1, SJ5.1, U1.2, U1.10, U1.25
GND2: C11.2, C12.2, C13.2, C14.2, C15.2, J17.1, J18.1, J19.1, J20.1, J22.1, R24.1, R25.1, R30.1, SJ9.1, U3.2, U3.10, U3.25
GND3: C16.2, C17.2, C18.2, C19.2, C20.2, J25.1, J26.1, J27.1, J28.1, J30.1, R34.1, R35.1, R40.1, SJ13.1, U4.2, U4.10, U4.25
GND4: C21.2, C22.2, C23.2, C24.2, C25.2, J33.1, J34.1, J35.1, J36.1, J38.1, R44.1, R45.1, R50.1, SJ17.1, U5.2, U5.10, U5.25
GND5: C26.2, C27.2, C28.2, C29.2, C30.2, J41.1, J42.1, J43.1, J44.1, J46.1, R54.1, R55.1, R60.1, SJ21.1, U6.2, U6.10, U6.25
GND6: C31.2, C32.2, C33.2, C34.2, C35.2, J49.1, J50.1, J51.1, J52.1, J54.1, R64.1, R65.1, R70.1, SJ25.1, U7.2, U7.10, U7.25
GND7: C36.2, C37.2, C38.2, C39.2, C40.2, J57.1, J58.1, J59.1, J60.1, J62.1, R74.1, R75.1, R80.1, SJ29.1, U8.2, U8.10, U8.25
GND8: C41.2, C42.2, C43.2, C44.2, C45.2, J65.1, J66.1, J67.1, J68.1, J70.1, R84.1, R85.1, R90.1, SJ33.1, U9.2, U9.10, U9.25
GND9: C46.2, C47.2, C48.2, C49.2, C50.2, J73.1, J74.1, J75.1, J76.1, J78.1, R94.1, R95.1, R100.1, SJ37.1, U10.2, U10.10, U10.25
GND10: C51.2, C52.2, C53.2, C54.2, C55.2, J81.1, J82.1, J83.1, J84.1, J86.1, R104.1, R105.1, R110.1, SJ41.1, U11.2, U11.10, U11.25
GND11: C56.2, C57.2, C58.2, C59.2, C60.2, J89.1, J90.1, J91.1, J92.1, J94.1, R114.1, R115.1, R120.1, SJ45.1, U12.2, U12.10, U12.25
GND12: C61.2, C62.2, C63.2, C64.2, C65.2, J97.1, J98.1, J99.1, J100.1, J102.1, R124.1, R125.1, R130.1, SJ49.1, U13.2, U13.10, U13.25
GND13: C66.2, C67.2, C68.2, C69.2, C70.2, J105.1, J106.1, J107.1, J108.1, J110.1, R134.1, R135.1, R140.1, SJ53.1, U14.2, U14.10, U14.25
GND14: C71.2, C72.2, C73.2, C74.2, C75.2, J113.1, J114.1, J115.1, J116.1, J118.1, R144.1, R145.1, R150.1, SJ57.1, U15.2, U15.10, U15.25
GND15: C76.2, C77.2, C78.2, C79.2, C80.2, J121.1, J122.1, J123.1, J124.1, J126.1, R154.1, R155.1, R160.1, SJ61.1, U16.2, U16.10, U16.25
GND16: C81.2, C82.2, C83.2, C84.2, C85.2, J129.1, J130.1, J131.1, J132.1, J134.1, R164.1, R165.1, R170.1, SJ65.1, U17.2, U17.10, U17.25
GND17: C86.2, C87.2, C88.2, C89.2, C90.2, J137.1, J138.1, J139.1, J140.1, J142.1, R174.1, R175.1, R180.1, SJ69.1, U18.2, U18.10, U18.25
GND18: C91.2, C92.2, C93.2, C94.2, C95.2, J145.1, J146.1, J147.1, J148.1, J150.1, R184.1, R185.1, R190.1, SJ73.1, U19.2, U19.10, U19.25
GND19: C96.2, C97.2, C98.2, C99.2, C100.2, J153.1, J154.1, J155.1, J156.1, J158.1, R194.1, R195.1, R200.1, SJ77.1, U20.2, U20.10, U20.25
GND20: C101.2, C102.2, C103.2, C104.2, C105.2, J161.1, J162.1, J163.1, J164.1, J166.1, R204.1, R205.1, R210.1, SJ81.1, U21.2, U21.10, U21.25
GND21: C106.2, C107.2, C108.2, C109.2, C110.2, J169.1, J170.1, J171.1, J172.1, J174.1, R214.1, R215.1, R220.1, SJ85.1, U22.2, U22.10, U22.25
GND22: C111.2, C112.2, C113.2, C114.2, C115.2, J177.1, J178.1, J179.1, J180.1, J182.1, R224.1, R225.1, R230.1, SJ89.1, U23.2, U23.10, U23.25
GND23: C116.2, C117.2, C118.2, C119.2, C120.2, J185.1, J186.1, J187.1, J188.1, J190.1, R234.1, R235.1, R240.1, SJ93.1, U24.2, U24.10, U24.25
GND24: C121.2, C122.2, C123.2, C124.2, C125.2, J193.1, J194.1, J195.1, J196.1, J198.1, R244.1, R245.1, R250.1, SJ97.1, U25.2, U25.10, U25.25
GND25: C126.2, C127.2, C128.2, C129.2, C130.2, J201.1, J202.1, J203.1, J204.1, J206.1, R254.1, R255.1, R260.1, SJ101.1, U26.2, U26.10, U26.25
GND26: C131.2, C132.2, C133.2, C134.2, C135.2, J209.1, J210.1, J211.1, J212.1, J214.1, R264.1, R265.1, R270.1, SJ105.1, U27.2, U27.10, U27.25
GND27: C136.2, C137.2, C138.2, C139.2, C140.2, J217.1, J218.1, J219.1, J220.1, J222.1, R274.1, R275.1, R280.1, SJ109.1, U28.2, U28.10, U28.25
GND28: C141.2, C142.2, C143.2, C144.2, C145.2, J225.1, J226.1, J227.1, J228.1, J230.1, R284.1, R285.1, R290.1, SJ113.1, U29.2, U29.10, U29.25
GND29: C146.2, C147.2, C148.2, C149.2, C150.2, J233.1, J234.1, J235.1, J236.1, J238.1, R294.1, R295.1, R300.1, SJ117.1, U30.2, U30.10, U30.25
GND30: C151.2, C152.2, C153.2, C154.2, C155.2, J241.1, J242.1, J243.1, J244.1, J246.1, R304.1, R305.1, R310.1, SJ121.1, U31.2, U31.10, U31.25
GND31: C156.2, C157.2, C158.2, C159.2, C160.2, J249.1, J250.1, J251.1, J252.1, J254.1, R314.1, R315.1, R320.1, SJ125.1, U32.2, U32.10, U32.25
GND32: C161.2, C162.2, C163.2, C164.2, C165.2, J257.1, J258.1, J259.1, J260.1, J262.1, R324.1, R325.1, R330.1, SJ129.1, U33.2, U33.10, U33.25
GND33: C166.2, C167.2, C168.2, C169.2, C170.2, J265.1, J266.1, J267.1, J268.1, J270.1, R334.1, R335.1, R340.1, SJ133.1, U34.2, U34.10, U34.25
GND34: C171.2, C172.2, C173.2, C174.2, C175.2, J273.1, J274.1, J275.1, J276.1, J278.1, R344.1, R345.1, R350.1, SJ137.1, U35.2, U35.10, U35.25
GND35: C176.2, C177.2, C178.2, C179.2, C180.2, J281.1, J282.1, J283.1, J284.1, J286.1, R354.1, R355.1, R360.1, SJ141.1, U36.2, U36.10, U36.25
GND36: C181.2, C182.2, C183.2, C184.2, C185.2, J289.1, J290.1, J291.1, J292.1, J294.1, R364.1, R365.1, R370.1, SJ145.1, U37.2, U37.10, U37.25
GND37: C186.2, C187.2, C188.2, C189.2, C190.2, J297.1, J298.1, J299.1, J300.1, J302.1, R374.1, R375.1, R380.1, SJ149.1, U38.2, U38.10, U38.25
GND38: C191.2, C192.2, C193.2, C194.2, C195.2, J305.1, J306.1, J307.1, J308.1, J310.1, R384.1, R385.1, R390.1, SJ153.1, U39.2, U39.10, U39.25
GND39: C196.2, C197.2, C198.2, C199.2, C200.2, J313.1, J314.1, J315.1, J316.1, J318.1, R394.1, R395.1, R400.1, SJ157.1, U40.2, U40.10, U40.25
unnamed: C5.1, U2.27, Y1.P$2
unnamed: C3.1, U2.26, Y1.P$1
unnamed: D1.C, R2.2
unnamed: C10.1, U1.27, Y2.P$2
unnamed: C9.1, U1.26, Y2.P$1
unnamed: D2.C, R20.2
unnamed: C15.1, U3.27, Y3.P$2
unnamed: C14.1, U3.26, Y3.P$1
unnamed: D3.C, R30.2
unnamed: C20.1, U4.27, Y4.P$2
unnamed: C19.1, U4.26, Y4.P$1
unnamed: D4.C, R40.2
unnamed: C25.1, U5.27, Y5.P$2
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
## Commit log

2018-04-11 added bno080 to sfe lib
2018-04-12 adding Nates BNO080
2018-04-13 updated to Nates BNO080
2018-04-13 pre review
2018-04-13 post design review
2018-04-13 Adding panel files
2018-04-24 fixed rotation in processing sketch
2018-11-25 Added an if statement to check if inQuat length is 4 before proceeding. Formatting.
    Without an if statement that checks the length of inQuat, an ArrayIndexOutOfBoundsException occasionally occurs. This is because the data retrieved from the sensor is not guaranteed to be 4 tokens lo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
2023-11-14 Update Notes
